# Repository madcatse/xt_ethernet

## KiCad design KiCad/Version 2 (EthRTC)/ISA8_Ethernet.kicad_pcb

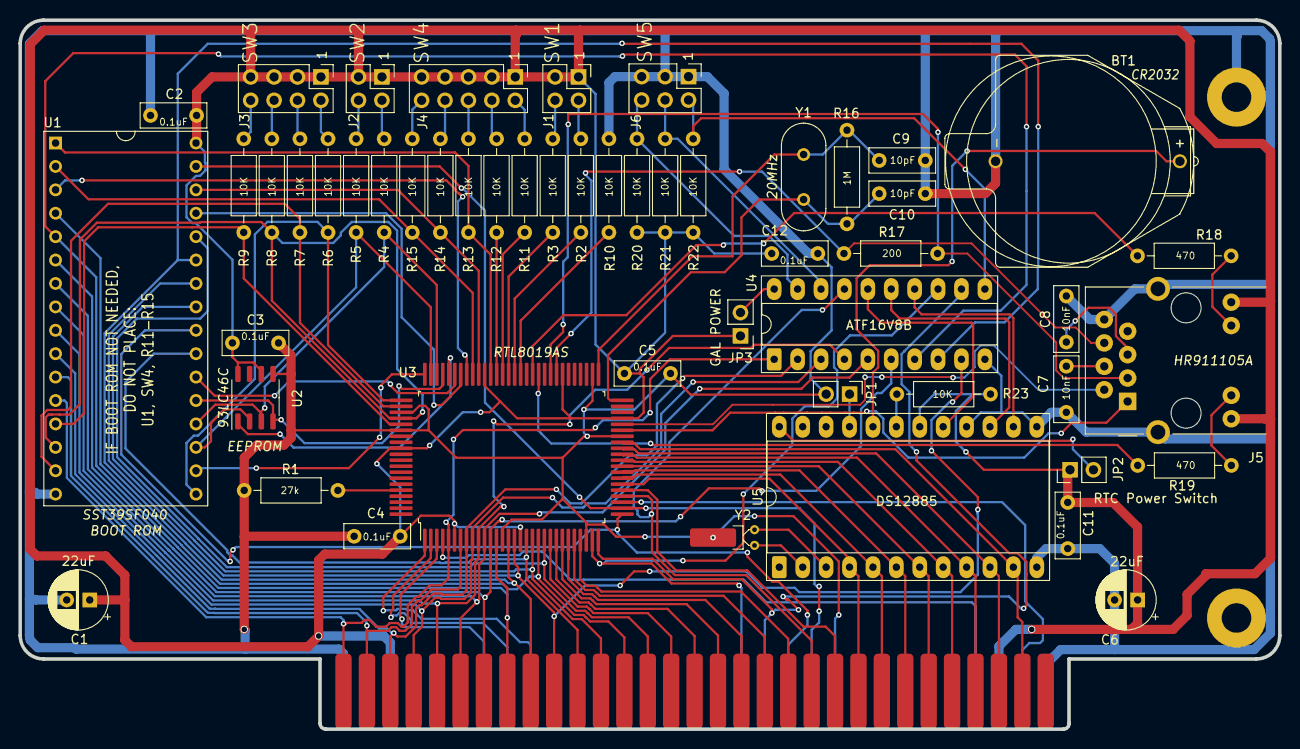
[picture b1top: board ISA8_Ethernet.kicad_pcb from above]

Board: 2 copper layers, 136.7 x 76.9 mm, 56 parts (1 on the bottom side), 100 nets.

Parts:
BT1: CR2032; Battery_Holder_CR2032_Universal
BUS1: BUSPC_DEV; Conn_Edge_PCB_ISA8
C1, C6: 22uF; CP_Radial_D6.3mm_P2.50mm
C2, C3, C4, C5, C11, C12: 0.1uF; C_Disc_D7.0mm_W2.5mm_P5.00mm
C7, C8: 10nF; C_Disc_D7.0mm_W2.5mm_P5.00mm
C9, C10: 10pF; C_Disc_D7.0mm_W2.5mm_P5.00mm
G1: LOGO; set_dont_get_it
HOLE1, HOLE2: M3; MountingHole_3.2mm_M3_Pad_Via
J1, J2: Conn_02x02_Odd_Even; PinHeader_2x02_P2.54mm_Vertical
J3: Conn_02x04_Odd_Even; PinHeader_2x04_P2.54mm_Vertical
J4: Conn_02x05_Odd_Even; PinHeader_2x05_P2.54mm_Vertical
J5: HR911105A; RJ45_HR911105A
J6: Conn_02x03_Odd_Even; PinHeader_2x03_P2.54mm_Vertical
JP1: Clear CMOS; PinHeader_1x02_P2.54mm_Vertical
JP2: RTC_POWER; PinHeader_1x02_P2.54mm_Vertical
JP3: GAL Power; PinHeader_1x02_P2.54mm_Vertical
R1: 27k; R_Axial_DIN0207_L6.3mm_D2.5mm_P10.16mm_Horizontal
R2, R3, R4, R5, R6, R7, R8, R9, R10, R11, R12, R13, R14, R15, R20, R21, R22, R23: 10K; R_Axial_DIN0207_L6.3mm_D2.5mm_P10.16mm_Horizontal
R16: 1M; R_Axial_DIN0207_L6.3mm_D2.5mm_P10.16mm_Horizontal
R17: 200; R_Axial_DIN0207_L6.3mm_D2.5mm_P10.16mm_Horizontal
R18, R19: 470; R_Axial_DIN0207_L6.3mm_D2.5mm_P10.16mm_Horizontal
U1: SST39SF040; Socket_DIP32_600
U2: 93LC46C; SO-8_3.9x4.9mm_P1.27mm
U3: RTL8019AS; IC_PQFP-100_14x20mm_P0.65mm_Hand_Soldering
U4: ATF16V8B; DIP-20_W7.62mm_Socket_LongPads
U5: DS12885; DIP-24_W15.24mm_Socket_LongPads
Y1: 20MHz; Crystal_HC-49U_Vert
Y2: 32768Hz; Crystal_DS15_D1.5mm_L5.0mm_Horizontal_1EP_style1

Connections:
/A0: BUS1.62 (SA0), U1.12 (A0), U3.5 (SA0), U4.1 (I/CLK)
/A1: BUS1.61 (SA1), U1.11 (A1), U3.7 (SA1)
/A2: BUS1.60 (SA2), U1.10 (A2), U3.8 (SA2), U4.2 (I1)
/A3: BUS1.59 (SA3), U1.9 (A3), U3.9 (SA3), U4.3 (I2)
/A4: BUS1.58 (SA4), U1.8 (A4), U3.10 (SA4), U4.4 (I3)
/A5: BUS1.57 (SA5), U1.7 (A5), U3.11 (SA5), U4.5 (I4)
/A6: BUS1.56 (SA6), U1.6 (A6), U3.12 (SA6), U4.6 (I5)
/A7: BUS1.55 (SA7), U1.5 (A7), U3.13 (SA7), U4.7 (I6)
/A8: BUS1.54 (SA8), U1.27 (A8), U3.15 (SA8), U4.8 (I7)
/A9: BUS1.53 (SA9), U1.26 (A9), U3.16 (SA9), U4.9 (I8)
/A10: BUS1.52 (SA10), U1.23 (A10), U3.18 (SA10)
/A11: BUS1.51 (SA11), U1.25 (A11), U3.19 (SA11)
/A12: BUS1.50 (SA12), U1.4 (A12), U3.20 (SA12)
/A13: BUS1.49 (SA13), U1.28 (A13), U3.21 (SA13)
/A14: BUS1.48 (SA14), U3.22 (SA14)
/A15: BUS1.47 (SA15), U3.23 (SA15)
/A16: BUS1.46 (SA16), U3.24 (SA16)
/A17: BUS1.45 (SA17), U3.25 (SA17)
/A18: BUS1.44 (SA18), U3.26 (SA18)
/A19: BUS1.43 (SA19), U3.27 (SA19)
/AEN: BUS1.42 (AEN), U3.34 (AEN), U4.17 (I/O3)
/AS0: J6.6, R20.1, U4.19 (I/O1)
/AS1: J6.4, R21.1, U4.18 (I/O2)
/AS2: J6.2, R22.1, U4.11 (I9/~OE)
/AUI: R10.1, U3.64 (AUI)
/BA14: U1.29 (A14), U3.74 (BA14/PL0)
/BA15: U1.3 (A15), U3.73 (BA15)
/BA16: R15.1, U1.2 (A16), U3.72 (BA16/BS4)
/BA17: R14.1, U1.30 (A17), U3.71 (BA17/BS3)
/BA18: R13.1, U1.1 (A18), U3.69 (BA18/BS2)
/BA19: R12.1, U3.68 (BA19/BS1)
/BA20: R11.1, U3.67 (BA20/BS0)
/BA21: R3.1, U3.66 (BA21/PNP)
/BD0: R9.1, U1.13 (DQ0), U3.85 (BD0/IOS3)
/BD1: R8.1, U1.14 (DQ1), U3.84 (BD1/IOS2)
/BD2: R7.1, U1.15 (DQ2), U3.82 (BD2/IOS1)
/BD3: R6.1, U1.17 (DQ3), U3.81 (BD3/IOS0)
/BD4: U1.18 (DQ4), U3.80 (BD4/IRQS2)
/BD5: R5.1, U1.19 (DQ5), U2.2 (SCLK), U3.79 (BD5/IRQS1/EESK)
/BD6: R4.1, U1.20 (DQ6), U2.3 (DI), U3.78 (BD6/IRQS0/EEDI)
/BD7: U1.21 (DQ7), U2.4 (DO), U3.77 (BD7/PL1/EEDO)
/D0: BUS1.40 (SD0), U3.36 (SD0), U5.4 (AD0)
/D1: BUS1.39 (SD1), U3.37 (SD1), U5.5 (AD1)
/D2: BUS1.38 (SD2), U3.38 (SD2), U5.6 (AD2)
/D3: BUS1.37 (SD3), U3.39 (SD3), U5.7 (AD3)
/D4: BUS1.36 (SD4), U3.40 (SD4), U5.8 (AD4)
/D5: BUS1.35 (SD5), U3.41 (SD5), U5.9 (AD5)
/D6: BUS1.34 (SD6), U3.42 (SD6), U5.10 (AD6)
/D7: BUS1.33 (SD7), U3.43 (SD7), U5.11 (AD7)
/EECS: U2.1 (CS), U3.76 (EECS)
/IOCHRDY: BUS1.41 (IO_READY), U3.35 (IOCHRDY)
/IRQ3: BUS1.25 (IRQ3), U3.3 (INT1/IRQ3)
/IRQ4: BUS1.24 (IRQ4), U3.2 (INT2/IRQ4)
/IRQ5: BUS1.23 (IRQ5), U3.1 (INT3/IRQ5)
/IRQ9: BUS1.4 (IRQ2), U3.4 (INT0/IRQ2/9)
/JP: R2.1, U3.65 (JP)
/LED_CRS: R18.2, U3.62 (LED1/LED_RX/LED_CRS)
/LED_LINK: R19.2, U3.61 (LED0/LED_COL/LED_LINK)
/RSTDRV: BUS1.2 (RESET), U3.33 (RSTDRV)
/RTCALE: U4.14 (I/O6), U5.14 (AS)
/RTCRD: U4.16 (I/O4), U5.17 (DS)
/RTCWR: U4.15 (I/O5), U5.15 (R/~W)
/TP_RX+: J5.R3 (RD+), R17.1, U3.59 (TPIN+)
/TP_RX-: J5.R6 (RD-), R17.2, U3.58 (TPIN-)
/TP_TX+: J5.R1 (TD+), U3.45 (TPOUT+)
/TP_TX-: J5.R2 (TD-), U3.46 (TPOUT-)
/~BCS: U1.22 (~CE), U3.75 (~BCSB)
/~IOCS16: R1.2, U3.96 (~IOCS16B/SLOT16)
/~IOR: BUS1.14 (IOR), U3.29 (~IORB), U4.13 (I/O7)
/~IOW: BUS1.13 (IOW), U3.30 (~IOWB), U4.12 (I/O8)
/~IRQ: R23.1, U5.19 (~IRQ)
/~SMEMR: BUS1.12 (MEMR), U1.24 (~OE), U3.31 (~SMEMRB)
/~SMEMW: BUS1.11 (MEMW), U1.31 (~WE), U3.32 (~SMEMWB)
GND: BT1.2 (-), BUS1.1 (GND), BUS1.10 (GND), BUS1.31 (GND), C1.2, C2.2, C3.2, C4.2, C5.2, C6.2, C7.2, C8.2, C9.1, C10.1, C11.2, C12.2, HOLE1.1, HOLE2.1, J5.13 (SHIELD), J5.R8 (GND), J6.1, J6.3, J6.5, JP1.2 (B), R1.1, R10.2, U1.16 (GND), U2.5 (GND), U3.14 (GND), U3.28 (GND), U3.44 (GND), U3.52 (GND), U3.83 (GND), U3.86 (GND), U4.10 (GND), U5.12 (GND), U5.13 (~CS), U5.16 (GND), Y2.3
unnamed: BT1.1 (+), U5.20 (VBAT)
unnamed: J1.2, R2.2
unnamed: J1.4, R3.2
unnamed: J2.2, R4.2
unnamed: J2.4, R5.2
unnamed: J3.2, R6.2
unnamed: J3.4, R7.2
unnamed: J3.6, R8.2
unnamed: J3.8, R9.2
unnamed: J4.2, R11.2
unnamed: J4.4, R12.2
unnamed: J4.6, R13.2
unnamed: J4.8, R14.2
unnamed: J4.10, R15.2
unnamed: J5.L3 (LEDG_K), R19.1
unnamed: J5.L2 (LEDY_K), R18.1
unnamed: C8.1, J5.R5 (RCT)
unnamed: C7.1, J5.R4 (TCT)
unnamed: JP1.1 (A), U5.21 (~RCLR)
unnamed: JP2.2 (B), U5.24 (VCC)
unnamed: JP3.2 (B), U4.20 (VCC)
unnamed: C10.2, R16.1, U3.50 (X1), Y1.1
unnamed: C9.2, R16.2, U3.51 (X2), Y1.2
unnamed: U5.2 (X1), Y2.2
unnamed: U5.3 (X2), Y2.1
VCC: BUS1.3 (VCC), BUS1.29 (VCC), C1.1, C2.1, C3.1, C4.1, C5.1, C6.1, C11.1, C12.1, J1.1, J1.3, J2.1, J2.3, J3.1, J3.3, J3.5, J3.7, J4.1, J4.3, J4.5, J4.7, J4.9, J5.L1 (LEDY_A), J5.L4 (LEDG_A), JP2.1 (A), JP3.1 (A), R20.2, R21.2, R22.2, R23.2, U1.32 (VCC), U2.6 (ORG), U2.8 (VCC), U3.6 (VCC), U3.17 (VCC), U3.47 (VCC), U3.57 (VCC), U3.70 (VCC), U3.89 (VCC), U5.18 (~RESET)

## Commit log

2024-08-11 Rework
2024-10-09 update 10102024
2024-10-11 Version 0.1 ready gerbers
2024-12-09 Update for BOM
2024-12-30 Version 1.0 upload
2026-01-31 Added version 2 of EthRTC card
2026-02-01 Silkscreen finish
2026-02-04 Gerbers

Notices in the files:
KiCad/Version 2 (EthRTC)/ISA8_Ethernet.kicad_pcb:
Licensed under CERN-OHL-S: https://cern-ohl.web.cern.ch
